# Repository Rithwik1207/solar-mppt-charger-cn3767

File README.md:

# solar-mppt-charger-cn3767
Solar MPPT battery charger using CN3767 with LTC4412 power path management

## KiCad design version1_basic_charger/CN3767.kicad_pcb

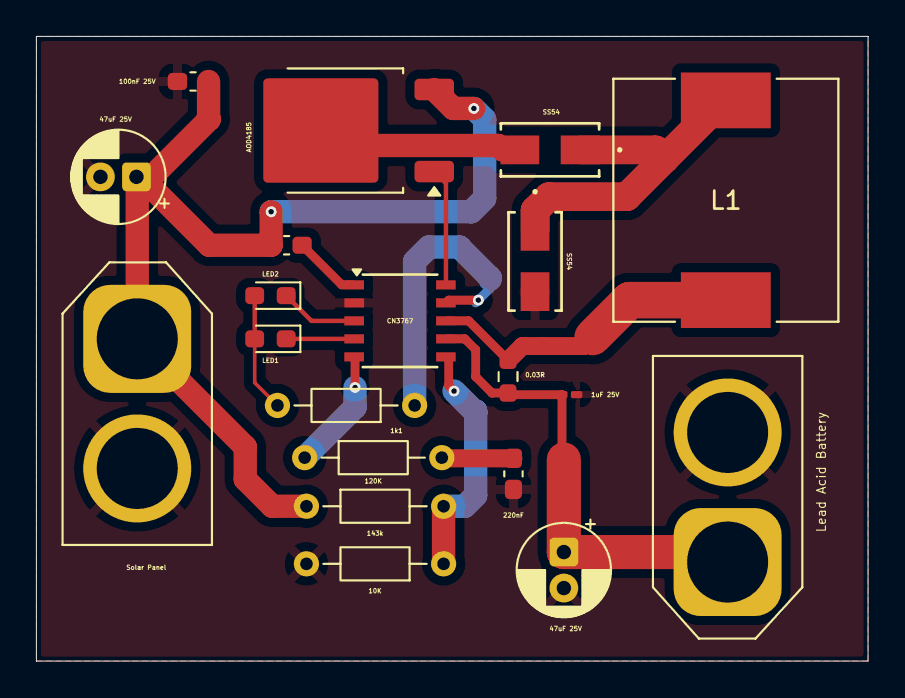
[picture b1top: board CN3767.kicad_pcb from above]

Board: 2 copper layers, 46.2 x 34.7 mm, 20 parts (0 on the bottom side), 15 nets.

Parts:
0.03R: 0.03R; R_0603_1608Metric_Pad0.98x0.95mm_HandSolder
1k1, 10K, 120K, 143k: R; R_Axial_DIN0204_L3.6mm_D1.6mm_P7.62mm_Horizontal
1uF 25V: C_0201_0603Metric_Pad0.64x0.40mm_HandSolder
47uF 25V: C_Polarized1; CP_Radial_D5.0mm_P2.00mm
47uF 25V#2: C_Polarized2; CP_Radial_D5.0mm_P2.00mm
100nF 25V: C_Polarized; C_0603_1608Metric_Pad1.08x0.95mm_HandSolder
220nF: C_0603_1608Metric_Pad1.08x0.95mm_HandSolder
AOD4185: AOD4185; TO-252-2
C3: 100nF; C_0603_1608Metric_Pad1.08x0.95mm_HandSolder
CN3767: CN3767; SSOP-10_3.9x4.9mm_P1.00mm
L1: 10uH; IND_SRP1265A-100M
LED1: LED; LED_0603_1608Metric_Pad1.05x0.95mm_HandSolder
LED2: LED1; LED_0603_1608Metric_Pad1.05x0.95mm_HandSolder
Lead Acid Battery: Battery_Cell; AMASS_XT60-M_1x02_P7.20mm_Vertical
SS54, SS54#2: SS54-HF; SDO_DO-214AC_CIP
Solar Panel: XT60 F; AMASS_XT60-F_1x02_P7.20mm_Vertical

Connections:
GND: 1uF 25V.2, 10K.2, 47uF 25V.2, 47uF 25V#2.2, 100nF 25V.2, 220nF.2, CN3767.2 (GND), Lead Acid Battery.2 (-), SS54#2.2, Solar Panel.2
unnamed: 47uF 25V.1, 100nF 25V.1, 143k.1, AOD4185.3, C3.1, Solar Panel.1
unnamed: 120K.2, 220nF.1
unnamed: L1.1, SS54.1, SS54#2.1
unnamed: AOD4185.2, SS54.2
unnamed: 0.03R.2, 1uF 25V.1, 47uF 25V#2.1, CN3767.7 (BAT), Lead Acid Battery.1 (+)
unnamed: 120K.1, CN3767.5 (COM)
unnamed: 0.03R.1, CN3767.8 (CSP), L1.2
unnamed: AOD4185.1, CN3767.10 (DRV)
unnamed: 10K.1, 143k.2, CN3767.6 (MPPT)
unnamed: 1k1.1, CN3767.9 (VCC)
unnamed: C3.2, CN3767.1 (VG)
unnamed: CN3767.3 (~CHRG), LED2.1 (K)
unnamed: CN3767.4 (~DONE), LED1.1 (K)
unnamed: 1k1.2, LED1.2 (A), LED2.2 (A)

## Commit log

2026-05-04 Create schematics
2026-05-04 Create pcb
2026-05-04 Create outputs
